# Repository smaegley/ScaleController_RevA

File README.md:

Scale Controller Rev-A

A custom ESP32-C3 scale controller PCB derived from the KLP-5e ESP32 Sensor Board. This design integrates an HX711 24-bit ADC and supports 4× half-bridge load cells, with output to a 0.96” SSD1306 OLED display over I²C. The board is designed to run ESPHome, making it easy to integrate into Home Assistant or other IoT ecosystems.

⸻

✨ Features
	•	ESP32-C3-WROOM-02-H4 module (RISC-V, Wi-Fi + BLE)
	•	USB-C connector for power, flashing and logs via the C3’s native USB-Serial/JTAG (USBLC6 ESD protection, no USB-UART bridge)
	•	Onboard LM1117 LDO regulator (5V → 3.3V)
	•	HX711 24-bit ADC for load cell integration
	•	4× JST-PH-3 connectors for half-bridge load cells (LC1/LC2 = S− pair, LC3/LC4 = S+ pair; any cell plugs into any socket)
	•	J9 4-pin header (back side) for an I²C OLED (SSD1306 128×64, 0.96”), 4.7k pull-ups on board
	•	Status LED D5 (green, GPIO7)
	•	Tare via the BOOT button (SW1, GPIO9) or Home Assistant — see the Rev-A button note below
	•	J6 expansion header (5-pin): 3V3, GPIO10, U0TXD, U0RXD, GND

Verified pin map (from the KiCad netlist):

| Function        | ESP32-C3 GPIO | Notes                             |
|-----------------|---------------|-----------------------------------|
| HX711 DOUT      | GPIO6         |                                   |
| HX711 PD_SCK    | GPIO5         |                                   |
| I²C SDA (OLED)  | GPIO4         |                                   |
| I²C SCL (OLED)  | GPIO3         |                                   |
| Tare button     | GPIO9         | reuses BOOT button SW1 (on board) |
| Status LED      | GPIO7         | D5, active-low                    |
| USB D−/D+       | GPIO18/GPIO19 | native USB, not usable as GPIO    |

⚠️ Rev-A boards: SW1 (BOOT) and SW2 (RESET) are wired across the switches’ internally
joined pins and short GPIO9 and EN to GND — the board will not start with them fitted.
Remove both (or cut one diagonal pair of legs on each). Details: docs/bringup-2026-11-01.md.

⸻

🛠️ Getting Started

Hardware Bring-Up Checklist
	1.	Power via USB-C → check +3.3V rail is stable.
	2.	Flash firmware/smoke-test.yaml (no Wi-Fi needed) → status LED blinks, logs on USB.
	3.	I²C scan → OLED should respond at 0x3C.
	4.	HX711 baseline → confirm stable raw counts with no load.
	5.	Plug one cell into LC1/LC2 and one into LC3/LC4 → pressing either moves the reading the same way.
	6.	Tare with empty platform.
	7.	Calibrate using a known mass (e.g. 1000 g). Compute calibration factor.

ESPHome Config

The full, ready-to-build configuration lives in firmware/scale-controller.yaml
(targets the ESP32-C3 with the verified pin map above). To use it:

	1.	Install ESPHome (pip install esphome or the Home Assistant add-on).
	2.	cp firmware/secrets.yaml.example firmware/secrets.yaml and fill in your Wi-Fi/API/OTA values.
	3.	esphome run firmware/scale-controller.yaml (first flash over USB-C, then OTA).

Key pins (see firmware/scale-controller.yaml for the complete config):

i2c:
  sda: GPIO4
  scl: GPIO3

sensor:
  - platform: hx711
    id: hx711_raw
    dout_pin: GPIO6
    clk_pin: GPIO5
    gain: 128

⸻

📂 Repo Structure
	•	KiCad project/ScaleController_RevA.kicad_pro — main KiCad project
	•	KiCad project/*.kicad_sch — schematics (root + ESP32-C3, HX711 load-cell summing, OLED header; user_interface is nested under the ESP32-C3 sheet)
	•	KiCad project/ScaleController_RevA.kicad_pcb — PCB layout (4-layer, routed, fabricated by PCBWay Sept 2026)
	•	firmware/scale-controller.yaml — ESPHome configuration
	•	firmware/smoke-test.yaml — bring-up firmware (USB logs only, no Wi-Fi)
	•	mechanical/ — load-cell puck models
	•	fabrication/ — Gerbers, BOM, pick-and-place (generated; gitignored)
	•	docs/ — bring-up notes, calibration steps

⸻

⚖️ License & Attribution

This project is licensed under the CERN Open Hardware Licence Version 2 – Strongly Reciprocal (CERN-OHL-S v2).

Derived from futureshocked/KLP-5e-ESP32-sensor-board.
Copyright © 2025 Steve Maegley
Copyright © 2022–2023 futureshocked

You are free to use, modify, manufacture, and distribute this design, provided that you release your modifications under the same license.

⸻

🚀 Next Steps
	•	Rev-A boards built and smoke-tested (Nov 2026): boot, USB, Wi-Fi and HX711 confirmed; button wiring error found
	•	Build the load-cell pucks and a test rig; calibrate and corner-test
	•	Rev-B: fix the button wiring; display mount; optional HX711 input filter
	•	Document calibration workflow with photos

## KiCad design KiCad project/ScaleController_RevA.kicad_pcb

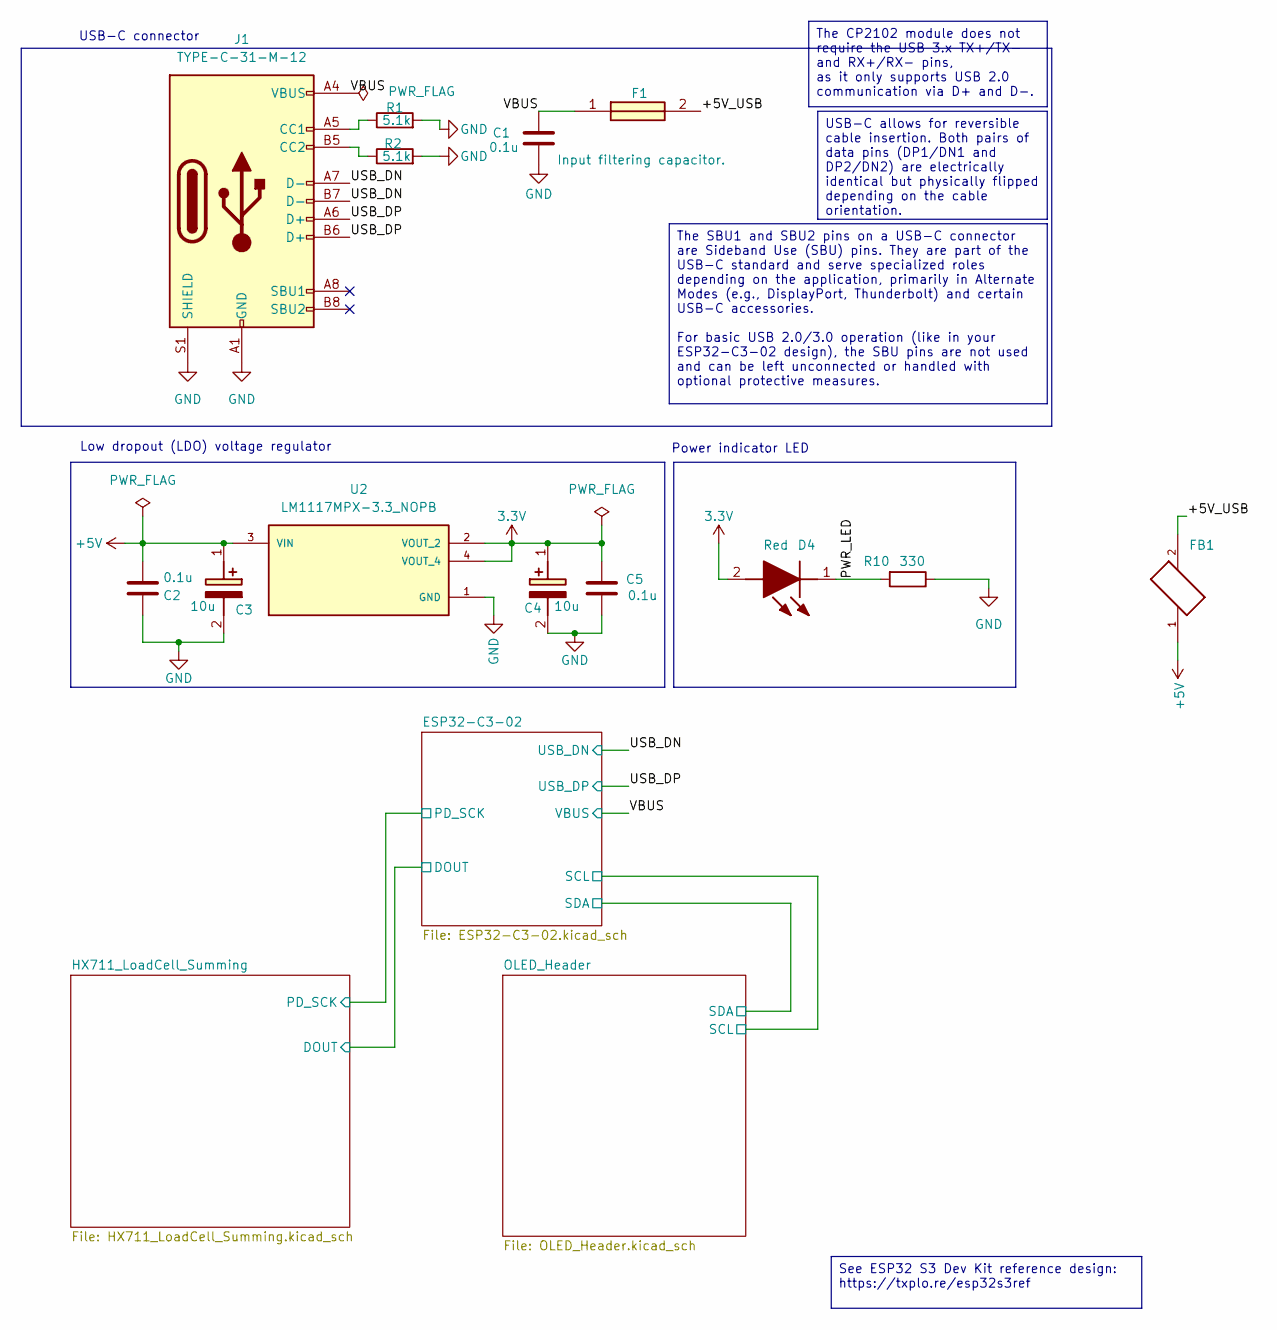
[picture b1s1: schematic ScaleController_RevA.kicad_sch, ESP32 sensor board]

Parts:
C1, C2, C5: 0.1u; C_0805_2012Metric; Voltage 1kV; Tolerance 100%
C3, C4: 10u; T491A; Voltage 1kV; Tolerance 100%; Manufacturer_Part_Number T491A106K010AT7280; Mouser Part Number 80-T491A106K107280
D4: Red; LEDC2012X120N; Manufacturer_Part_Number LTST-C170KRKT; Mouser Part Number 859-LTST-C170KRKT
F1: 0ZCH0110AF2E; FUSC3226X100N; Manufacturer_Part_Number 0ZCH0110AF2E
FB1: FBMJ2125HM330-T; BEADC2012X105N
J1: TYPE-C-31-M-12; USB_C_Receptacle_HRO_TYPE-C-31-M-12
R1, R2: 5.1k; R_0805_2012Metric
R10: 330; R_0805_2012Metric
U2: LM1117MPX-3.3_NOPB; VREG_LM1117MPX-3.3; Mouser Part Number 926-LM1117MPX3.3NOPB

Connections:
3.3V: C4.1 (+), C5.1, D4.2 (A), U2.2 (VOUT_2), U2.4 (VOUT_4); also elsewhere on the board
+5V: C2.1, C3.1 (+), FB1.1, U2.3 (VIN)
/+5V_USB: F1.2, FB1.2
/PWR_LED: D4.1 (K), R10.2
/USB_DN: J1.A7 (D-), J1.B7 (D-); also elsewhere on the board
/USB_DP: J1.A6 (D+), J1.B6 (D+); also elsewhere on the board
/VBUS: C1.1, F1.1, J1.A4 (VBUS), J1.A9 (VBUS), J1.B4 (VBUS), J1.B9 (VBUS); also elsewhere on the board
GND: C1.2, C2.2, C3.2 (-), C4.2 (-), C5.2, J1.A1 (GND), J1.A12 (GND), J1.B1 (GND), J1.B12 (GND), J1.S1 (SHIELD), R1.2, R2.2, R10.1, U2.1 (GND); also elsewhere on the board
unnamed: J1.A5 (CC1), R1.1
unnamed: J1.B5 (CC2), R2.1

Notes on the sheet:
USB-C connector
Power indicator LED
Low dropout (LDO) voltage regulator
The CP2102 module does not require the USB 3.x TX+/TX- and RX+/RX- pins, as it only supports USB 2.0 communication via D+ and D-.
See ESP32 S3 Dev Kit reference design: https://txplo.re/esp32s3ref
The SBU1 and SBU2 pins on a USB-C connector are Sideband Use (SBU) pins. They are part of the USB-C standard and serve specialized roles depending on the application, primarily in Alternate Modes (e.g., DisplayPort, Thunderbolt) and certain USB-C accessories. For basic USB 2.0/3.0 operation (like i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
USB-C allows for reversible cable insertion. Both pairs of data pins (DP1/DN1 and DP2/DN2) are electrically identical but physically flipped depending on the cable orientation.

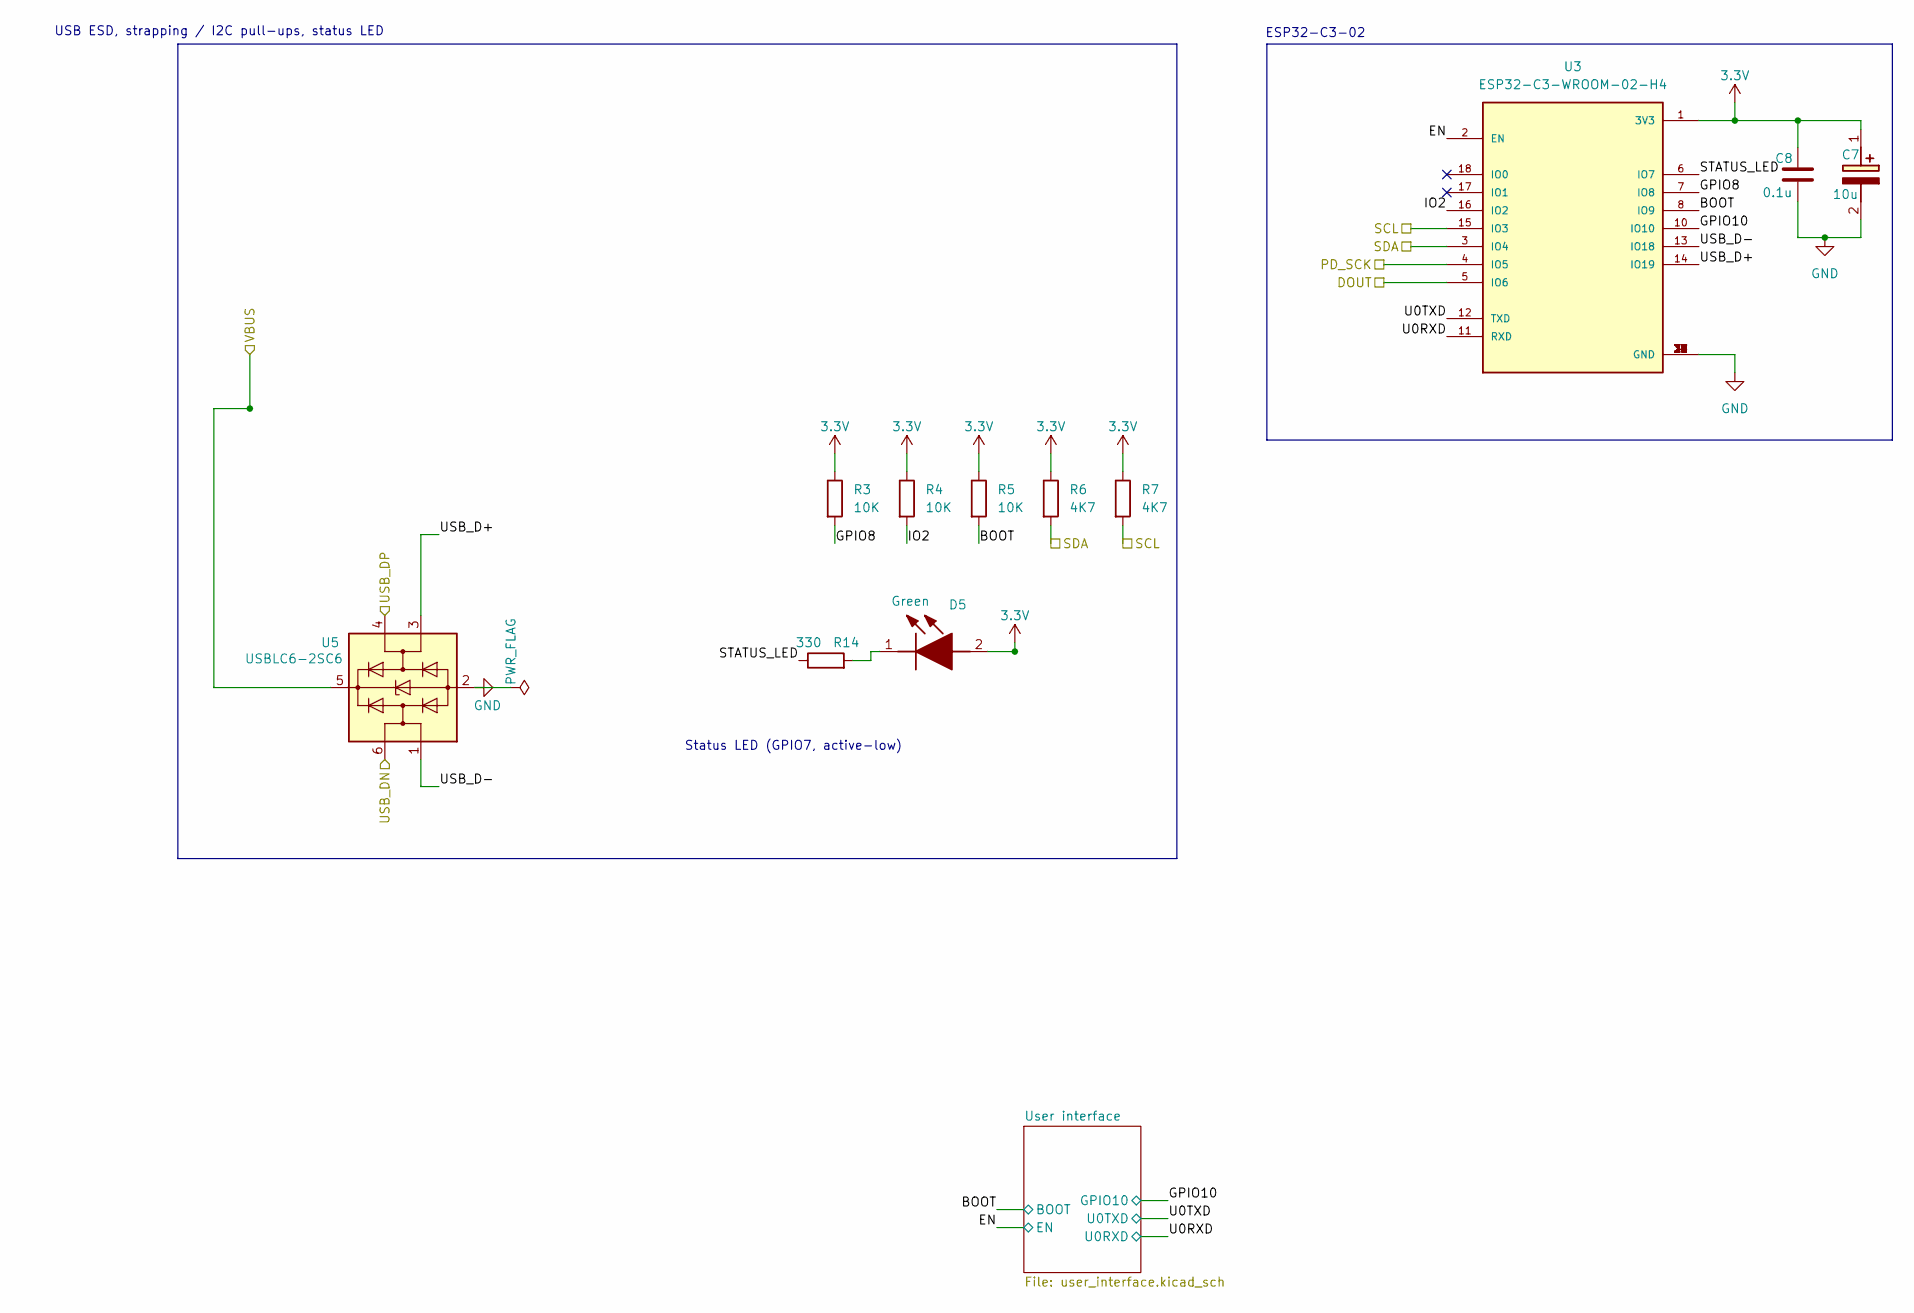
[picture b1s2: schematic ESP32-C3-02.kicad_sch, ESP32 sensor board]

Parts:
C7: 10u; T491A; Voltage 1kV; Tolerance 100%; Manufacturer_Part_Number T491A106K010AT7280; Mouser Part Number 80-T491A106K107280
C8: 0.1u; C_0805_2012Metric; Voltage 1kV; Tolerance 100%
D5: Green; LEDC2012X120N; Manufacturer_Part_Number LTST-C170GKT; Mouser Part Number 859-LTST-C170GKT
R3, R4, R5: 10K; R_0805_2012Metric
R6, R7: 4K7; R_0805_2012Metric
R14: 330; R_0805_2012Metric
U3: ESP32-C3-WROOM-02-H4; MODULE_ESP32-C3-WROOM-02-H4; Manufacturer_Part_Number ESP32-C3-WROOM-02-H4
U5: USBLC6-2SC6; SOT-23-6; Manufacturer_Part_Number USBLC6-2SC6; Mouser Part Number 511-USBLC6-2SC6

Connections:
3.3V: C7.1 (+), C8.1, D5.2 (A), R3.1, R4.1, R5.1, R6.1, R7.1, U3.1 (3V3); also elsewhere on the board
/ESP32-C3-02/BOOT: R5.2, U3.8 (IO9); also elsewhere on the board
/ESP32-C3-02/DOUT: U3.5 (IO6); also elsewhere on the board
/ESP32-C3-02/EN: U3.2 (EN); also elsewhere on the board
/ESP32-C3-02/GPIO8: R3.2, U3.7 (IO8)
/ESP32-C3-02/GPIO10: U3.10 (IO10); also elsewhere on the board
/ESP32-C3-02/IO2: R4.2, U3.16 (IO2)
/ESP32-C3-02/PD_SCK: U3.4 (IO5); also elsewhere on the board
/ESP32-C3-02/SCL: R7.2, U3.15 (IO3); also elsewhere on the board
/ESP32-C3-02/SDA: R6.2, U3.3 (IO4); also elsewhere on the board
/ESP32-C3-02/STATUS_LED: R14.1, U3.6 (IO7)
/ESP32-C3-02/U0RXD: U3.11 (RXD); also elsewhere on the board
/ESP32-C3-02/U0TXD: U3.12 (TXD); also elsewhere on the board
/ESP32-C3-02/USB_D+: U3.14 (IO19), U5.3 (I/O2)
/ESP32-C3-02/USB_D-: U3.13 (IO18), U5.1 (I/O1)
/USB_DN: U5.6 (I/O1); also elsewhere on the board
/USB_DP: U5.4 (I/O2); also elsewhere on the board
/VBUS: U5.5 (VBUS); also elsewhere on the board
GND: C7.2 (-), C8.2, U3.9 (GND), U3.19 (GND), U3.20 (GND), U3.21 (GND), U3.22 (GND), U3.23 (GND), U3.24 (GND), U3.25 (GND), U3.26 (GND), U3.27 (GND), U3.28 (GND), U3.29 (GND), U3.30 (GND), U3.31 (GND), U3.32 (GND), U3.33 (GND), U3.34 (GND), U3.35 (GND), U3.36 (GND), U3.37 (GND), U3.38 (GND), U3.39 (GND), U5.2 (GND); also elsewhere on the board
unnamed: D5.1 (K), R14.2

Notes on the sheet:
Status LED (GPIO7, active-low)
USB ESD, strapping / I2C pull-ups, status LED
ESP32-C3-02

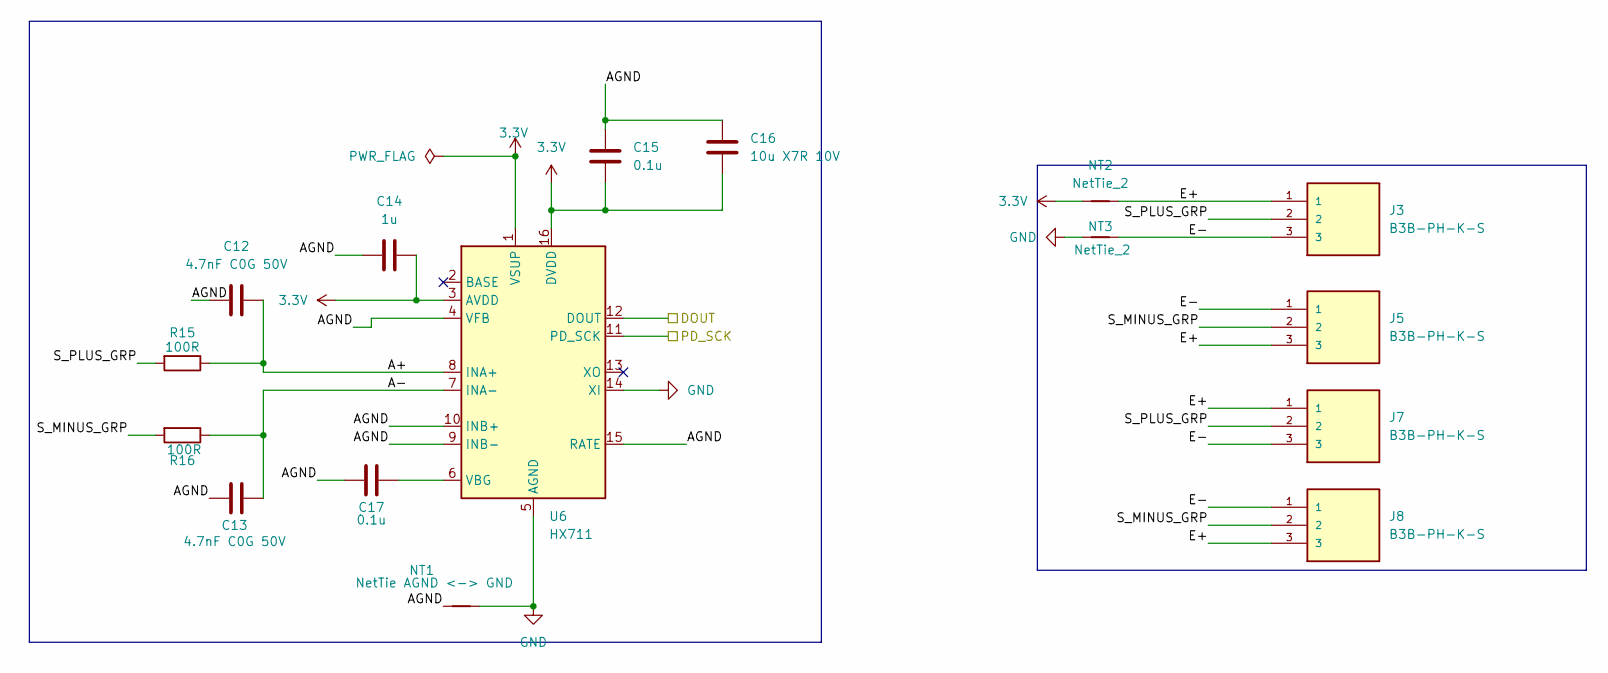
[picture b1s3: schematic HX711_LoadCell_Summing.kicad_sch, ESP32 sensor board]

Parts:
C12, C13: 4.7nF C0G 50V; C_0805_2012Metric
C14: 1u; C_0805_2012Metric
C15, C17: 0.1u; C_0805_2012Metric
C16: 10u X7R 10V; C_0805_2012Metric
J3, J5, J7, J8: B3B-PH-K-S; JST_PH_B3B-PH-K_1x03_P2.00mm_Vertical
NT1: NetTie AGND <-> GND; NetTie-2_SMD_Pad2.0mm
NT2, NT3: NetTie_2; NetTie-2_SMD_Pad2.0mm
R15, R16: 100R; R_0805_2012Metric
U6: HX711; SOIC-16_3.9x9.9mm_P1.27mm

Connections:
3.3V: C14.2, C15.2, C16.2, NT2.1, U6.1 (VSUP), U6.3 (AVDD), U6.16 (DVDD); also elsewhere on the board
/ESP32-C3-02/DOUT: U6.12 (DOUT); also elsewhere on the board
/ESP32-C3-02/PD_SCK: U6.11 (PD_SCK); also elsewhere on the board
/HX711_LoadCell_Summing/A+: C12.2, R15.1, U6.8 (INA+)
/HX711_LoadCell_Summing/A-: C13.1, R16.1, U6.7 (INA-)
/HX711_LoadCell_Summing/AGND: C12.1, C13.2, C14.1, C15.1, C16.1, C17.2, NT1.1, U6.4 (VFB), U6.9 (INB-), U6.10 (INB+), U6.15 (RATE)
/HX711_LoadCell_Summing/E+: J3.1, J5.3, J7.1, J8.3, NT2.2
/HX711_LoadCell_Summing/E-: J3.3, J5.1, J7.3, J8.1, NT3.2
/HX711_LoadCell_Summing/S_MINUS_GRP: J5.2, J8.2, R16.2
/HX711_LoadCell_Summing/S_PLUS_GRP: J3.2, J7.2, R15.2
GND: NT1.2, NT3.1, U6.5 (AGND), U6.14 (XI); also elsewhere on the board
unnamed: C17.1, U6.6 (VBG)

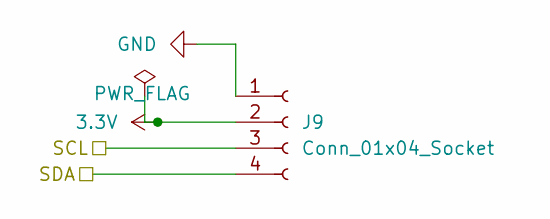
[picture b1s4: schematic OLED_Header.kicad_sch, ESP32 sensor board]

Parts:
J9: Conn_01x04_Socket; PinSocket_1x04_P2.54mm_Vertical

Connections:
3.3V: J9.2; also elsewhere on the board
/ESP32-C3-02/SCL: J9.3; also elsewhere on the board
/ESP32-C3-02/SDA: J9.4; also elsewhere on the board
GND: J9.1; also elsewhere on the board

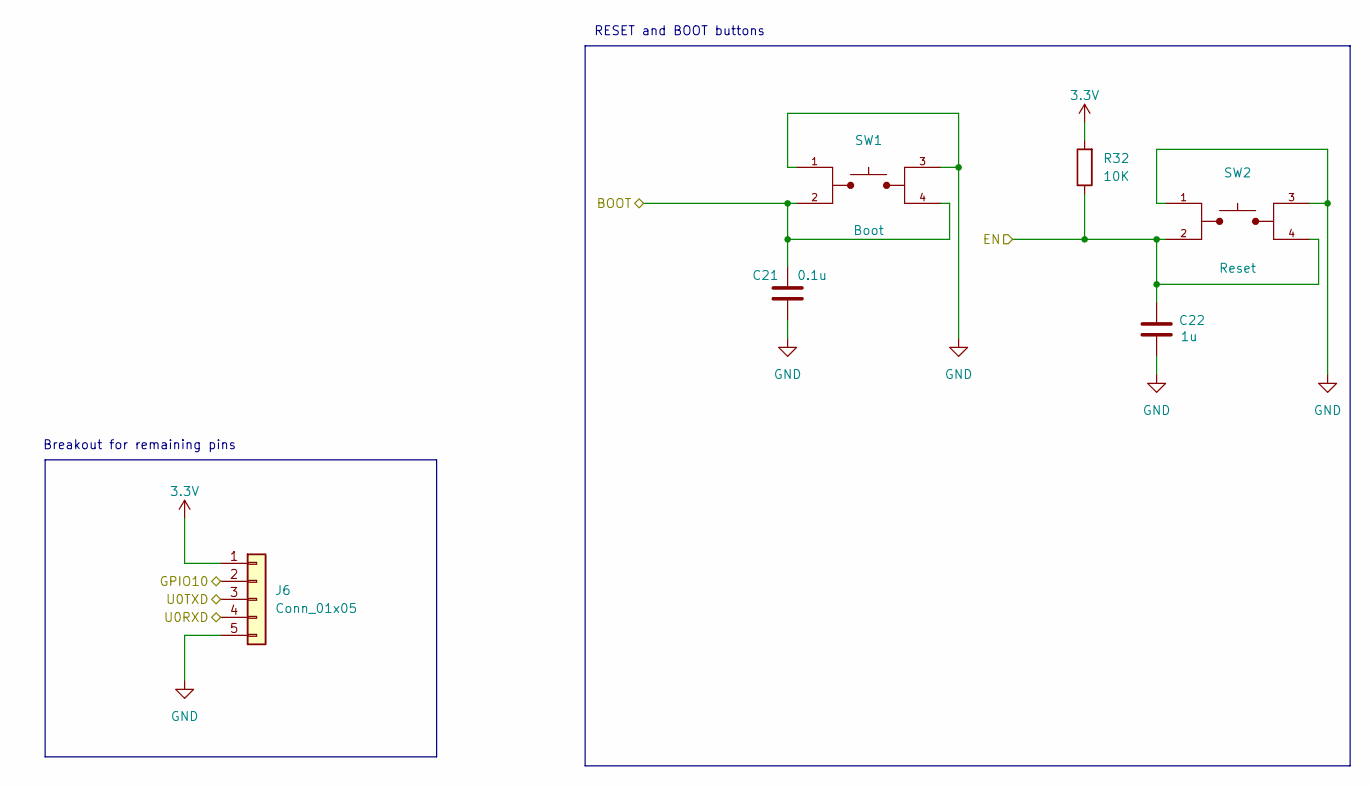
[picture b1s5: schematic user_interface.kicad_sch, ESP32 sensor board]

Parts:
C21: 0.1u; C_0805_2012Metric; Voltage 1kV; Tolerance 100%
C22: 1u; C_0805_2012Metric; Voltage 1kV; Tolerance 100%
J6: Conn_01x05; PinHeader_1x05_P2.54mm_Vertical
R32: 10K; R_0805_2012Metric
SW1, SW2: 1101NE; SW_TL3305AF260QG; Mfg Part# 8-004 SMD Button 8x3.6mm Height=2.5mm

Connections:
3.3V: J6.1, R32.2; also elsewhere on the board
/ESP32-C3-02/BOOT: C21.1, SW1.2, SW1.4; also elsewhere on the board
/ESP32-C3-02/EN: C22.1, R32.1, SW2.2, SW2.4; also elsewhere on the board
/ESP32-C3-02/GPIO10: J6.2; also elsewhere on the board
/ESP32-C3-02/U0RXD: J6.4; also elsewhere on the board
/ESP32-C3-02/U0TXD: J6.3; also elsewhere on the board
GND: C21.2, C22.2, J6.5, SW1.1, SW1.3, SW2.1, SW2.3; also elsewhere on the board

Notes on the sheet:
RESET and BOOT buttons
Breakout for remaining pins

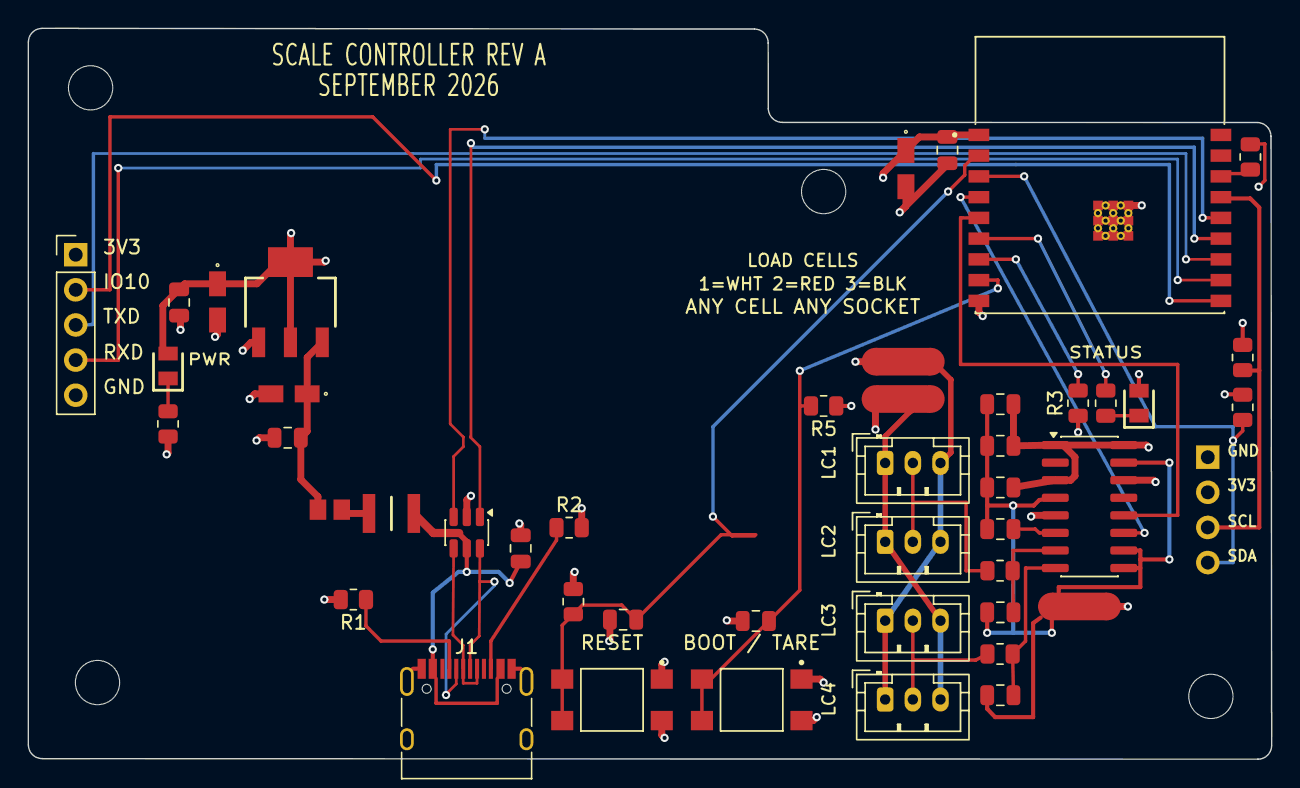
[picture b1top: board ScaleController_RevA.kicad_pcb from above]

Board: 4 copper layers, 89.9 x 52.8 mm, 52 parts (1 on the bottom side), 33 nets.

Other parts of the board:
DISP1: OLED 0.96in module (fit check only); OLED_0.96in_I2C_module_under
H1, H2, H3: MountingHole_3.2mm_M3
H4: b; MountingHole_3.2mm_M3

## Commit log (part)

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2025-08-25 Initial commit: forked from KLP-5e ESP32 sensor board
2025-08-25 Sanity commit to test push
2025-08-25 Add TODO.md and update README.md with project details
2025-08-25 Update .gitignore to ignore GIT_NOTES and local keys
2025-08-29 Rename project files from ESP32 sensor board.* to ScaleController_RevA.*
